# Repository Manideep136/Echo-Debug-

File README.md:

# Echo-Debug

 Echo Debug Gen3

## 📌 Project Overview

**Echo Debug Gen3** is a custom adapter PCB designed for the **Amazon Echo Gen 3**.

The Amazon Echo Gen 3 contains a hidden USB interface that can be accessed using this adapter board. The purpose of this PCB is to provide a clean and convenient connection to the internal USB interface instead of cutting a normal USB cable and manually soldering wires.

This project was designed using **KiCad** and includes the complete schematic, PCB layout, Bill of Materials (BOM), and manufacturing files.

---

## 🎯 Project Objectives

The main objectives of this project are:

- Design an adapter PCB for Amazon Echo Gen 3.
- Provide convenient access to the hidden USB interface.
- Connect the USB data lines correctly.
- Provide access to selected device voltage points.
- Learn practical USB PCB design.
- Understand differential-pair routing.
- Practice KiCad schematic and PCB design.
- Generate manufacturing-ready PCB files.

---

## 🔧 Main Features

- Designed specifically for Amazon Echo Gen 3.
- USB interface access.
- USB D+ and D− differential pair.
- Fastboot access.
- Device voltage test points/headers.
- Optional voltage indicator LEDs.
- Compact PCB design.
- Rounded PCB corners.
- KiCad source files included.
- Manufacturing files included.
- BOM included.

The original project's v1.1 revision corrected the USB differential-pair connection, removed zero-ohm resistors, added optional LEDs for +12 V and +1.9 V, rounded the PCB corners, and changed the USB connector to a lower-cost variant. :contentReference[oaicite:1]{index=1}

---

## 🧰 Tools Used

- KiCad
- KiCad Schematic Editor
- KiCad PCB Editor
- KiCad 3D Viewer
- USB interface
- Linux/Android debugging tools for testing

---

│   └── Project images
│
└── README.md

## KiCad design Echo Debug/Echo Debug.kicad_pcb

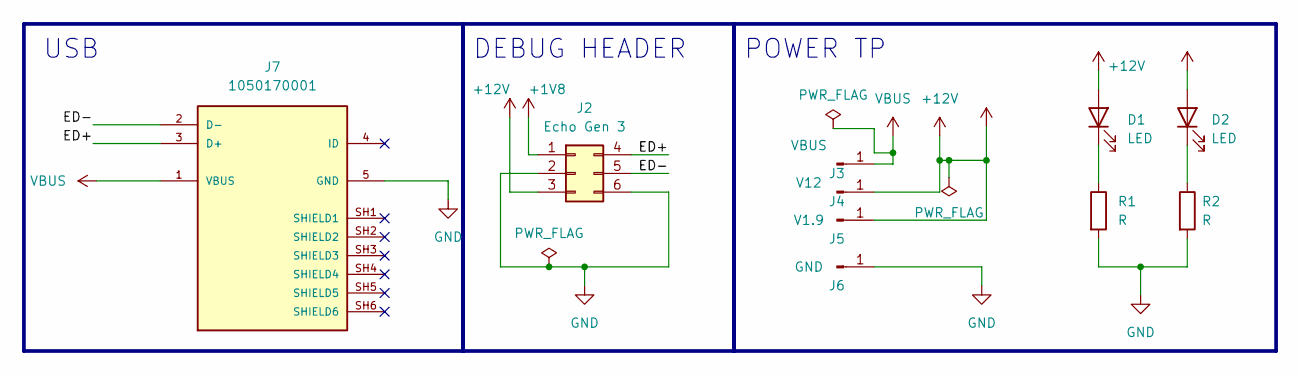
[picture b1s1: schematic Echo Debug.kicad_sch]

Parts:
D1, D2: LED; LED_0805_2012Metric
J2: Echo Gen 3; PinSocket_2x03_P2.54mm_Vertical
J3: VBUS; PinSocket_1x01_P2.54mm_Vertical
J4: V12; PinSocket_1x01_P2.54mm_Vertical
J5: V1.9; PinSocket_1x01_P2.54mm_Vertical
J6: GND; PinSocket_1x01_P2.54mm_Vertical
J7: 1050170001; MOLEX_1050170001
R1, R2: R; R_0805_2012Metric

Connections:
+12V: D1.2 (A), D2.2 (A), J2.1, J2.3, J4.1 (Pin_1_1), J5.1 (Pin_1_1)
/ED+: J2.4, J7.3 (D+)
/ED-: J2.5, J7.2 (D-)
GND: J2.2, J2.6, J6.1 (Pin_1_1), J7.5 (GND), R1.2, R2.2
unnamed: D1.1 (K), R1.1
unnamed: D2.1 (K), R2.1
VBUS: J3.1 (Pin_1_1), J7.1 (VBUS)

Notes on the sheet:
USB
DEBUG HEADER
POWER TP

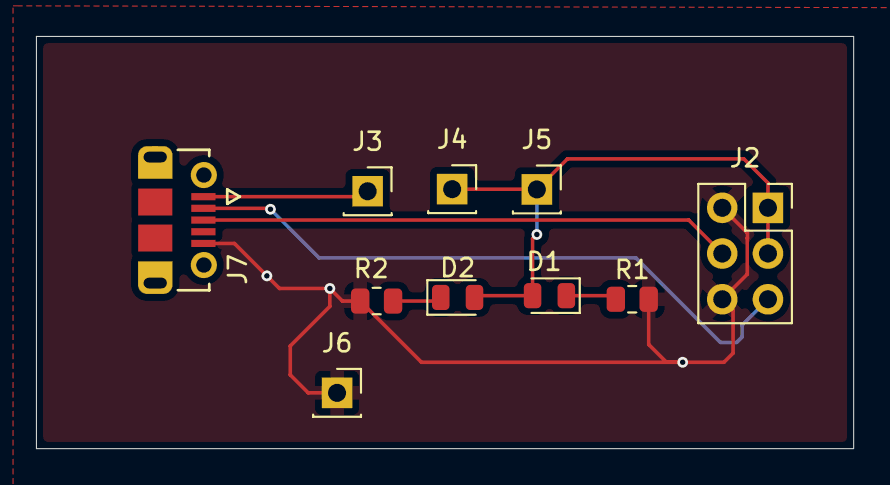
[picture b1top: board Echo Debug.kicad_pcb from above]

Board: 2 copper layers, 45.4 x 22.9 mm, 10 parts (0 on the bottom side), 7 nets.
